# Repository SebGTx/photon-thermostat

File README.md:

# photon-thermostat
Thermostat d'ambiance sur la base d'un Photon

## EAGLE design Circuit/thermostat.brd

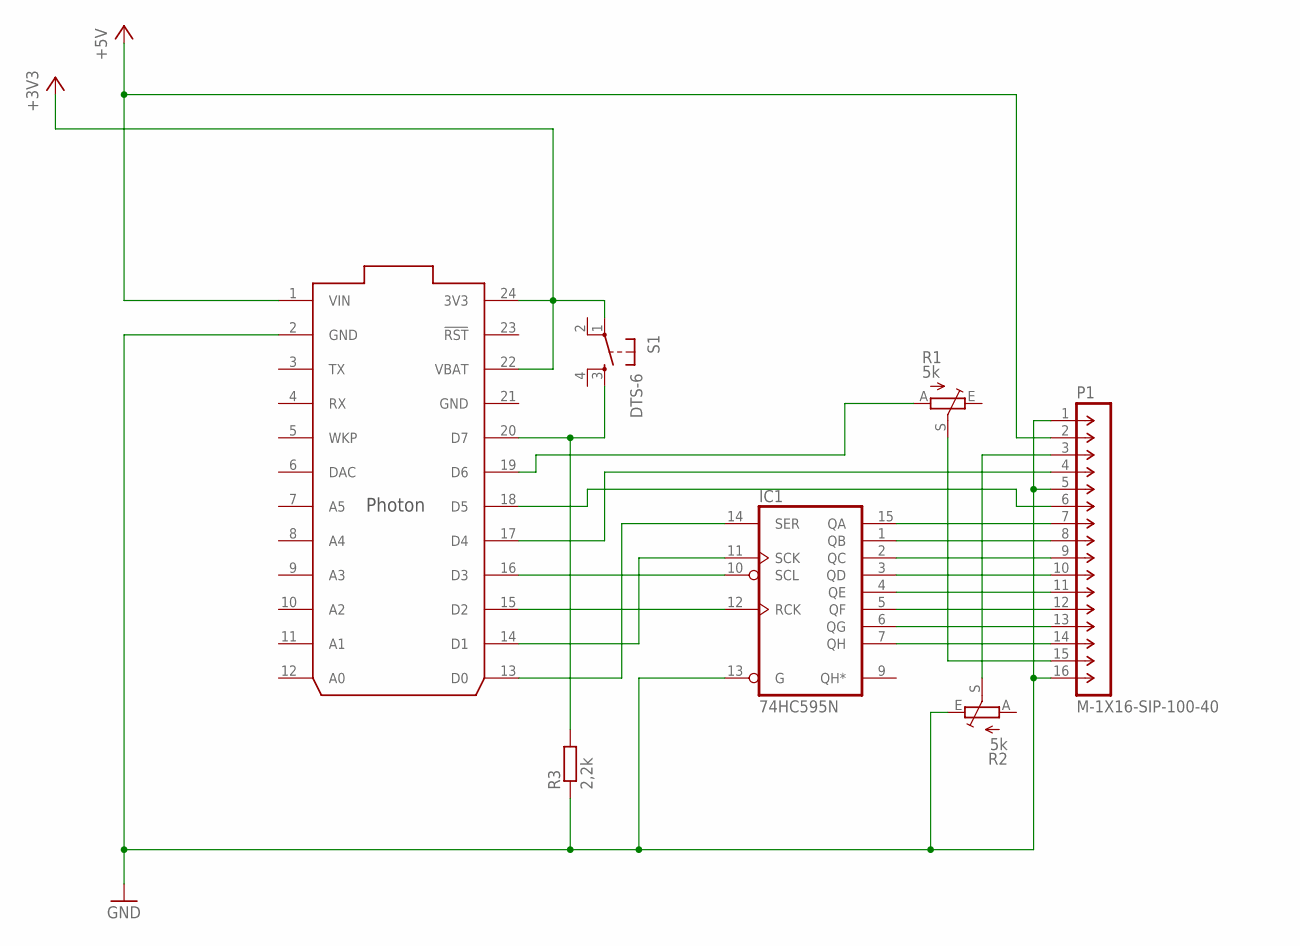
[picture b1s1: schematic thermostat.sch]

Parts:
IC1: 74HC595N; DIL16
P1: M-1X16-SIP-100-40; SIP-100-16-40
R1, R2: 5k; B25P
R3: 2,2k; 0207/10
S1: DTS-6
U$1: PHOTON_WITH_HEADERS; PHOTON

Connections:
+3V3: S1.1, U$1.22 (VBAT), U$1.24 (3V3)
+5V: P1.2, U$1.1 (VIN)
GND: IC1.8 (GND), IC1.13 (G), P1.1, P1.5, P1.16, R2.E, R3.1, U$1.2 (GND), U$1.21 (GND)
unnamed: IC1.14 (SER), U$1.13 (D0)
unnamed: IC1.11 (SCK), U$1.14 (D1)
unnamed: IC1.12 (RCK), U$1.15 (D2)
unnamed: IC1.10 (SCL), U$1.16 (D3)
unnamed: P1.4, U$1.17 (D4)
unnamed: P1.6, U$1.18 (D5)
unnamed: IC1.15 (QA), P1.7
unnamed: IC1.1 (QB), P1.8
unnamed: IC1.2 (QC), P1.9
unnamed: IC1.3 (QD), P1.10
unnamed: IC1.4 (QE), P1.11
unnamed: IC1.5 (QF), P1.12
unnamed: IC1.6 (QG), P1.13
unnamed: IC1.7 (QH), P1.14
unnamed: R3.2, S1.3, U$1.20 (D7)
unnamed: P1.3, R2.S
unnamed: R1.A, U$1.19 (D6)
unnamed: P1.15, R1.S
VCC: IC1.16 (VCC)

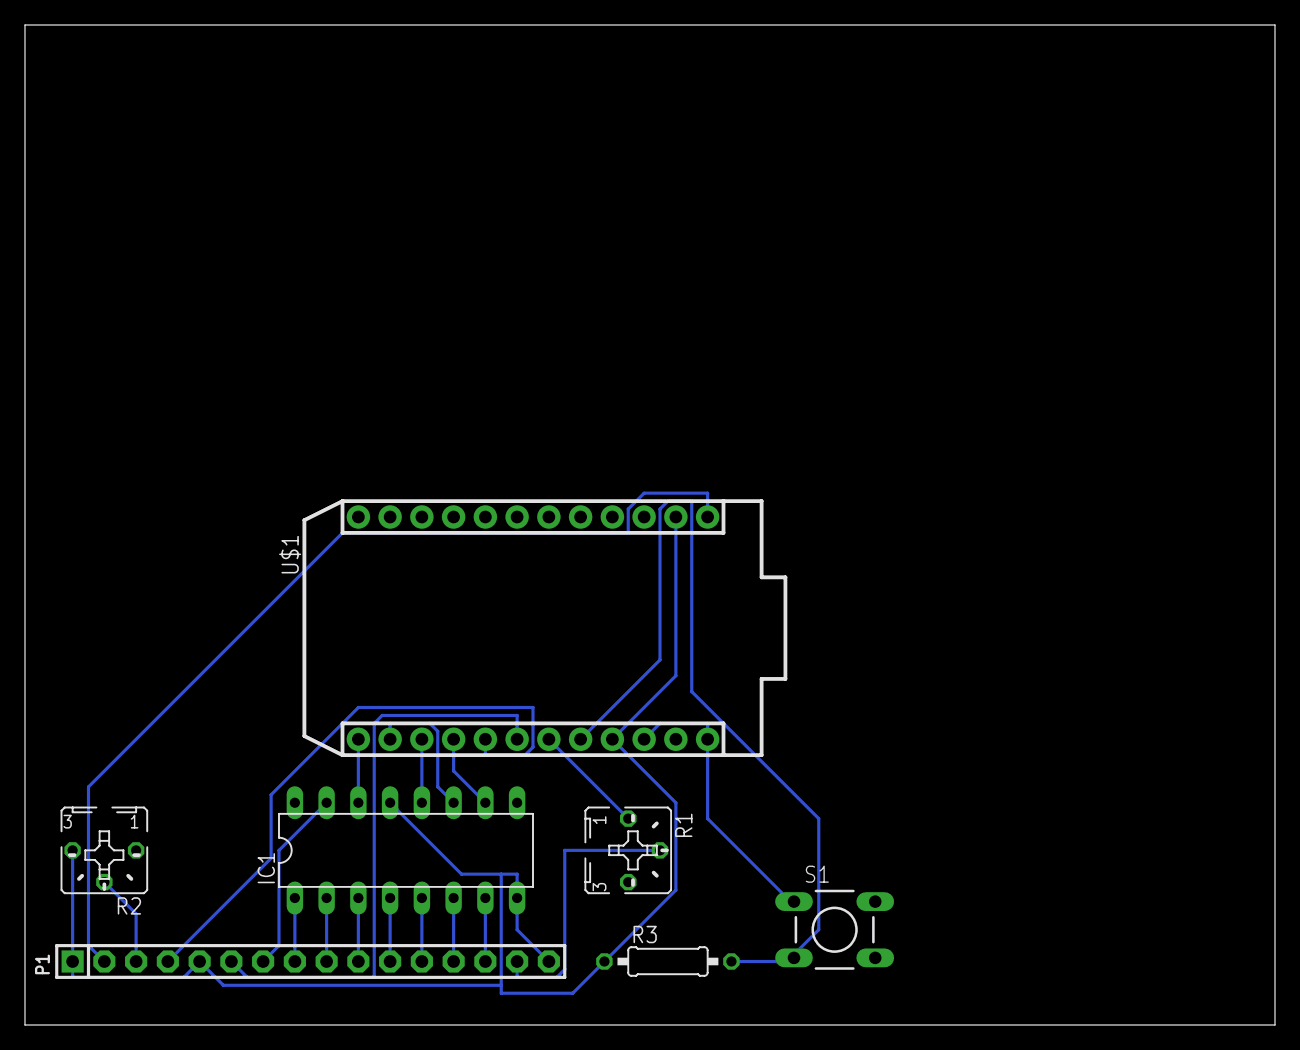
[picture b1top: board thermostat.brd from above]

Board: 2 copper layers, 100.0 x 80.0 mm, 7 parts (0 on the bottom side), 21 nets.

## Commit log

2015-10-31 2015-10-31
2015-11-14 Temperature sensor
    Add temperature sensor
2015-11-14 Gitignore Exclude Eagle Backup Files
2015-11-14 .gitignore
2015-11-14 Main programme rename
    Test.ino to Main.ino
2015-11-14 Characters improvment
2015-11-14 Minor change
2015-12-27 Temperature Bug problem
    Limit newTemperature between -10 and +10° from the last temperature
2020-07-25 Create LICENSE

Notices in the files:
parts and their libraries:
con-headers-jp: Copyright (C) 2008, Bob Starr
